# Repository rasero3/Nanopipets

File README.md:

# Nanopipets

MatLab(UART) --> FPGA(UART-SPI) --> DAC
ADC(SPI) --> FPGA(SPI-UART) --> MatLab(UART)

El DAC genera picos de la tension deseada cada 10Hz

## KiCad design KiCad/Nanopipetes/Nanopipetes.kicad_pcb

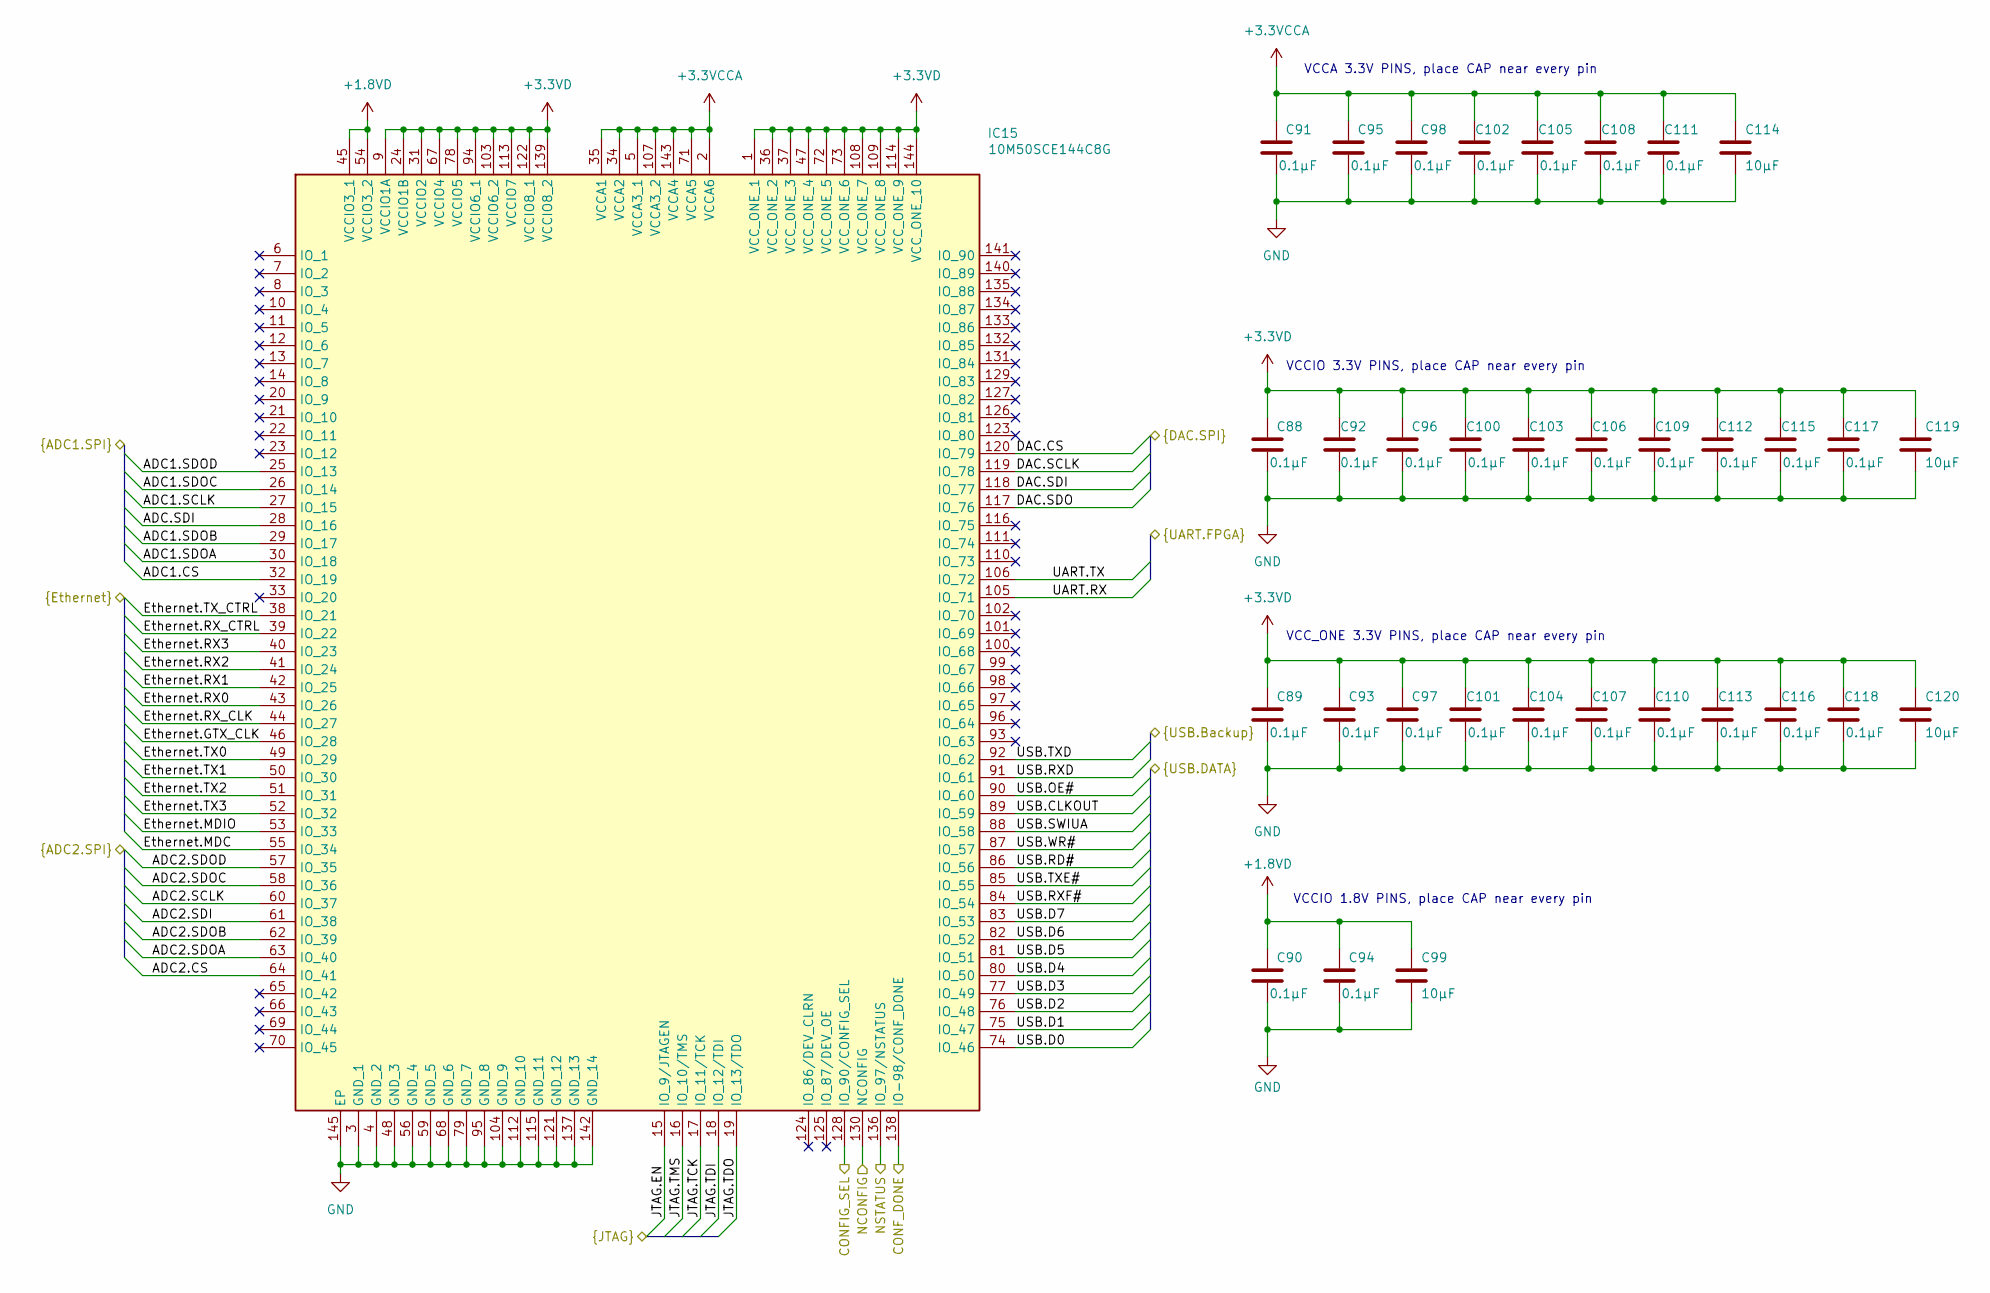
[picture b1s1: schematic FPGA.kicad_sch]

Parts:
C88, C89, C90, C91, C92, C93, C94, C95, C96, C97, C98, C100, C101, C102, C103, C104, C105, C106, C107, C108, C109, C110, C111, C112, C113, C115, C116, C117, C118: 0.1µF; C_0402_1005Metric; Mouser Part Number 581-0402YC104JAT4A
C99, C114, C119, C120: 10µF; C_0603_1608Metric; Mouser Part Number 80-C0603C106J3RACTU
IC15: 10M50SCE144C8G; QFP50P2200X2200X165-145N; Manufacturer_Part_Number 10M50SCE144C8G; Mouser Part Number 989-10M50SCE144C8G

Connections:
+1.8VD: C90.2, C94.2, C99.1, IC15.45 (VCCIO3_1), IC15.54 (VCCIO3_2); also elsewhere on the board
+3.3VCCA: C91.2, C95.2, C98.2, C102.2, C105.2, C108.2, C111.2, C114.1, IC15.2 (VCCA6), IC15.5 (VCCA3_1), IC15.34 (VCCA2), IC15.35 (VCCA1), IC15.71 (VCCA5), IC15.107 (VCCA3_2), IC15.143 (VCCA4); also elsewhere on the board
+3.3VD: C88.2, C89.2, C92.2, C93.2, C96.2, C97.2, C100.2, C101.2, C103.2, C104.2, C106.2, C107.2, C109.2, C110.2, C112.2, C113.2, C115.2, C116.2, C117.2, C118.2, C119.1, C120.1, IC15.1 (VCC_ONE_1), IC15.9 (VCCIO1A), IC15.24 (VCCIO1B), IC15.31 (VCCIO2), IC15.36 (VCC_ONE_2), IC15.37 (VCC_ONE_3), IC15.47 (VCC_ONE_4), IC15.67 (VCCIO4), IC15.72 (VCC_ONE_5), IC15.73 (VCC_ONE_6), IC15.78 (VCCIO5), IC15.94 (VCCIO6_1), IC15.103 (VCCIO6_2), IC15.108 (VCC_ONE_7), IC15.109 (VCC_ONE_8), IC15.113 (VCCIO7), IC15.114 (VCC_ONE_9), IC15.122 (VCCIO8_1), IC15.139 (VCCIO8_2), IC15.144 (VCC_ONE_10); also elsewhere on the board
/ADC1/ADC1.CS: IC15.32 (IO_19); also elsewhere on the board
/ADC1/ADC1.SCLK: IC15.27 (IO_15); also elsewhere on the board
/ADC1/ADC1.SDOA: IC15.30 (IO_18); also elsewhere on the board
/ADC1/ADC1.SDOB: IC15.29 (IO_17); also elsewhere on the board
/ADC1/ADC1.SDOC: IC15.26 (IO_14); also elsewhere on the board
/ADC1/ADC1.SDOD: IC15.25 (IO_13); also elsewhere on the board
/ADC1/ADC.SDI: IC15.28 (IO_16); also elsewhere on the board
/ADC2/ADC2.CS: IC15.64 (IO_41); also elsewhere on the board
/ADC2/ADC2.SCLK: IC15.60 (IO_37); also elsewhere on the board
/ADC2/ADC2.SDI: IC15.61 (IO_38); also elsewhere on the board
/ADC2/ADC2.SDOA: IC15.63 (IO_40); also elsewhere on the board
/ADC2/ADC2.SDOB: IC15.62 (IO_39); also elsewhere on the board
/ADC2/ADC2.SDOC: IC15.58 (IO_36); also elsewhere on the board
/ADC2/ADC2.SDOD: IC15.57 (IO_35); also elsewhere on the board
/Connectors/CONFIG_SEL: IC15.128 (IO_90/CONFIG_SEL); also elsewhere on the board
/Connectors/CONF_DONE: IC15.138 (IO-98/CONF_DONE); also elsewhere on the board
/Connectors/JTAG.EN: IC15.15 (IO_9/JTAGEN)
/Connectors/JTAG.TCK: IC15.17 (IO_11/TCK); also elsewhere on the board
/Connectors/JTAG.TDI: IC15.18 (IO_12/TDI); also elsewhere on the board
/Connectors/JTAG.TDO: IC15.19 (IO_13/TDO); also elsewhere on the board
/Connectors/JTAG.TMS: IC15.16 (IO_10/TMS); also elsewhere on the board
/Connectors/NCONFIG: IC15.130 (NCONFIG); also elsewhere on the board
/Connectors/NSTATUS: IC15.136 (IO_97/NSTATUS); also elsewhere on the board
/Connectors/UART.RX: IC15.105 (IO_71); also elsewhere on the board
/Connectors/UART.TX: IC15.106 (IO_72); also elsewhere on the board
/DAC/DAC.CS: IC15.120 (IO_79); also elsewhere on the board
/DAC/DAC.SCLK: IC15.119 (IO_78); also elsewhere on the board
/DAC/DAC.SDI: IC15.118 (IO_77); also elsewhere on the board
/DAC/DAC.SDO: IC15.117 (IO_76); also elsewhere on the board
/Ethernet/Ethernet.GTX_CLK: IC15.46 (IO_28); also elsewhere on the board
/Ethernet/Ethernet.MDC: IC15.55 (IO_34); also elsewhere on the board
/Ethernet/Ethernet.MDIO: IC15.53 (IO_33); also elsewhere on the board
/Ethernet/Ethernet.RX0: IC15.43 (IO_26); also elsewhere on the board
/Ethernet/Ethernet.RX1: IC15.42 (IO_25); also elsewhere on the board
/Ethernet/Ethernet.RX2: IC15.41 (IO_24); also elsewhere on the board
/Ethernet/Ethernet.RX3: IC15.40 (IO_23); also elsewhere on the board
/Ethernet/Ethernet.RX_CLK: IC15.44 (IO_27); also elsewhere on the board
/Ethernet/Ethernet.RX_CTRL: IC15.39 (IO_22); also elsewhere on the board
/Ethernet/Ethernet.TX0: IC15.49 (IO_29); also elsewhere on the board
/Ethernet/Ethernet.TX1: IC15.50 (IO_30); also elsewhere on the board
/Ethernet/Ethernet.TX2: IC15.51 (IO_31); also elsewhere on the board
/Ethernet/Ethernet.TX3: IC15.52 (IO_32); also elsewhere on the board
/Ethernet/Ethernet.TX_CTRL: IC15.38 (IO_21); also elsewhere on the board
/FPGA/USB.CLKOUT: IC15.89 (IO_59); also elsewhere on the board
/FPGA/USB.D0: IC15.74 (IO_46); also elsewhere on the board
/FPGA/USB.D1: IC15.75 (IO_47); also elsewhere on the board
/FPGA/USB.D2: IC15.76 (IO_48); also elsewhere on the board
/FPGA/USB.D3: IC15.77 (IO_49); also elsewhere on the board
/FPGA/USB.D4: IC15.80 (IO_50); also elsewhere on the board
/FPGA/USB.D5: IC15.81 (IO_51); also elsewhere on the board
/FPGA/USB.D6: IC15.82 (IO_52); also elsewhere on the board
/FPGA/USB.D7: IC15.83 (IO_53); also elsewhere on the board
/FPGA/USB.OE#: IC15.90 (IO_60); also elsewhere on the board
/FPGA/USB.RD#: IC15.86 (IO_56); also elsewhere on the board
/FPGA/USB.RXD: IC15.91 (IO_61); also elsewhere on the board
/FPGA/USB.RXF#: IC15.84 (IO_54); also elsewhere on the board
/FPGA/USB.SWIUA: IC15.88 (IO_58); also elsewhere on the board
/FPGA/USB.TXD: IC15.92 (IO_62); also elsewhere on the board
/FPGA/USB.TXE#: IC15.85 (IO_55); also elsewhere on the board
/FPGA/USB.WR#: IC15.87 (IO_57); also elsewhere on the board
GND: C88.1, C89.1, C90.1, C91.1, C92.1, C93.1, C94.1, C95.1, C96.1, C97.1, C98.1, C99.2, C100.1, C101.1, C102.1, C103.1, C104.1, C105.1, C106.1, C107.1, C108.1, C109.1, C110.1, C111.1, C112.1, C113.1, C114.2, C115.1, C116.1, C117.1, C118.1, C119.2, C120.2, IC15.3 (GND_1), IC15.4 (GND_2), IC15.48 (GND_3), IC15.56 (GND_4), IC15.59 (GND_5), IC15.68 (GND_6), IC15.79 (GND_7), IC15.95 (GND_8), IC15.104 (GND_9), IC15.112 (GND_10), IC15.115 (GND_11), IC15.121 (GND_12), IC15.137 (GND_13), IC15.142 (GND_14), IC15.145 (EP); also elsewhere on the board

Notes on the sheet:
VCC_ONE 3.3V PINS, place CAP near every pin
VCCA 3.3V PINS, place CAP near every pin
VCCIO 1.8V PINS, place CAP near every pin
VCCIO 3.3V PINS, place CAP near every pin

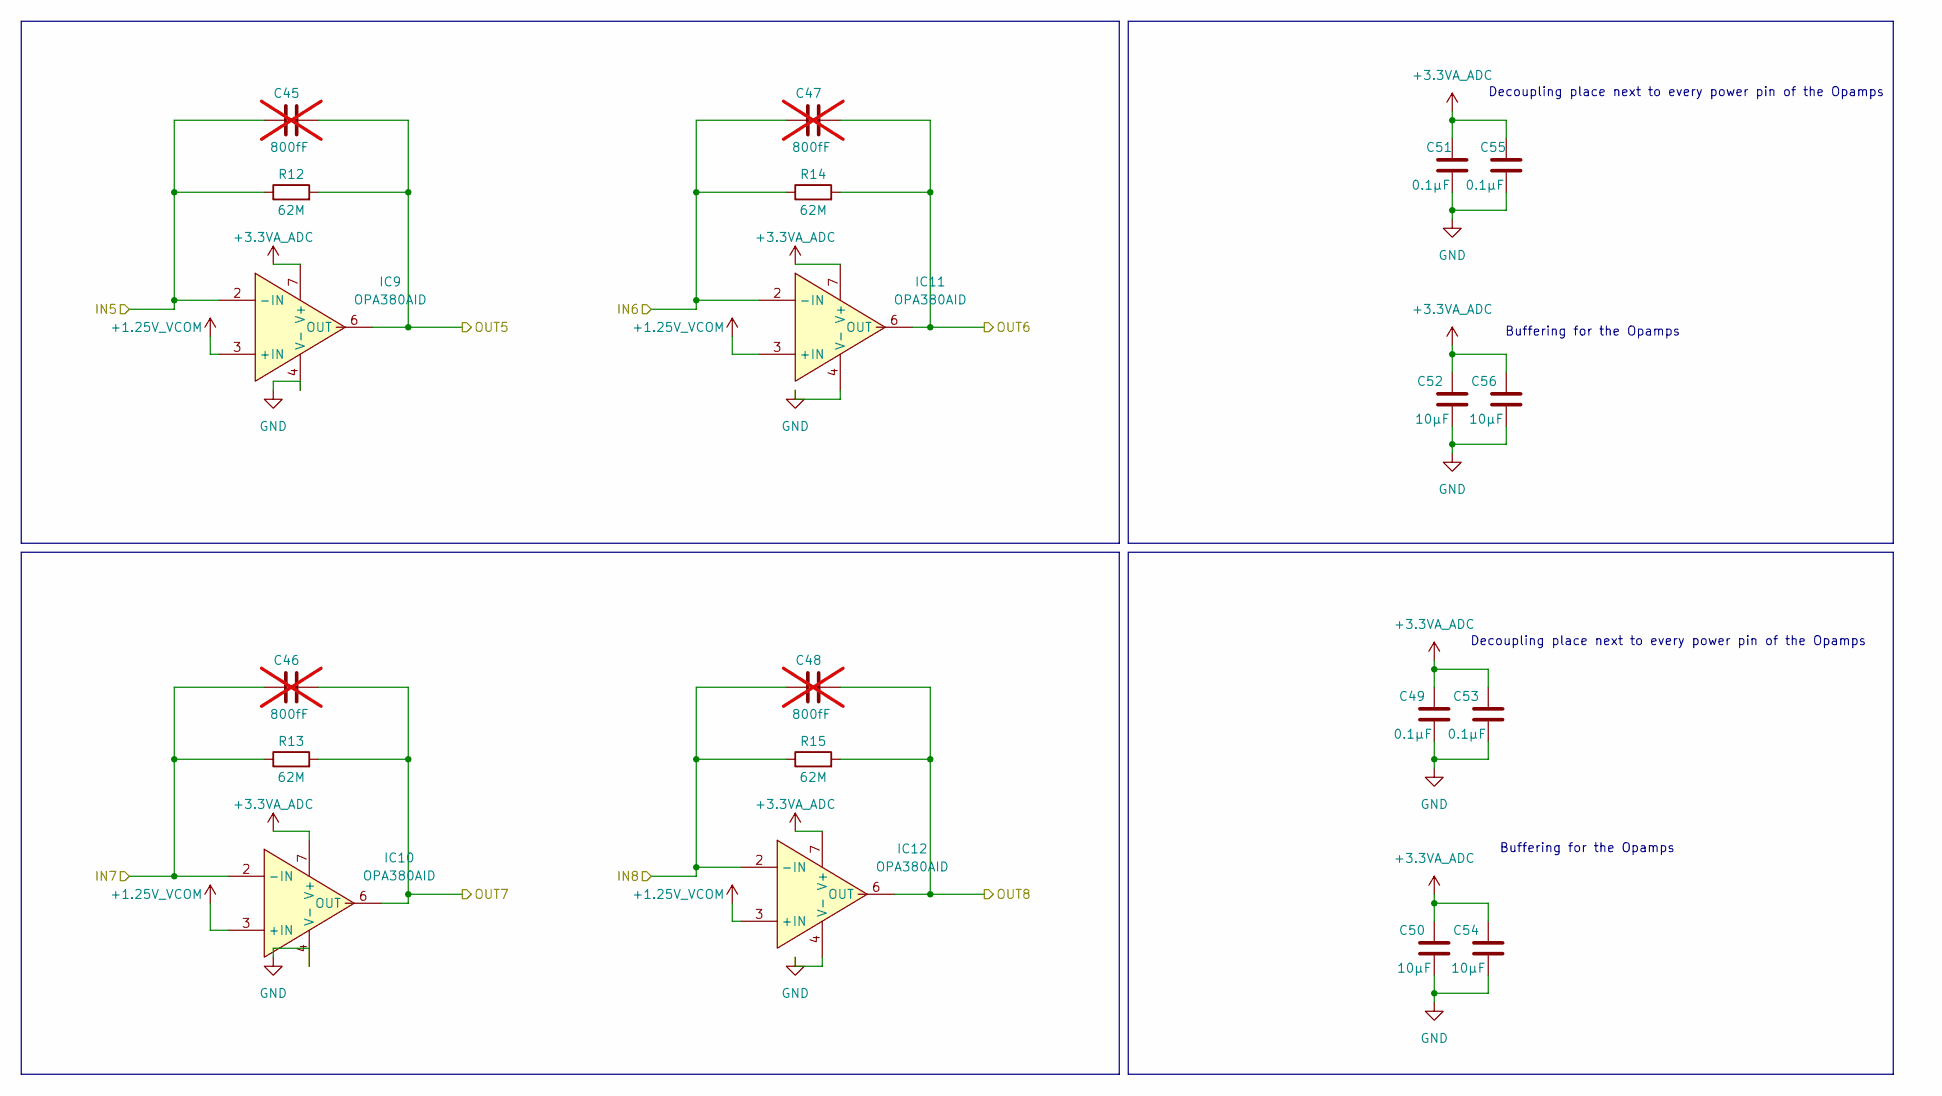
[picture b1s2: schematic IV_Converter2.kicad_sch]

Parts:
C45, C46, C47, C48: 800fF; C_0402_1005Metric; Mouser Part Number 81-GCM1555C2AR80BE2D; not fitted
C49, C51, C53, C55: 0.1µF; C_0402_1005Metric; Mouser Part Number 581-0402YC104JAT4A
C50, C52, C54, C56: 10µF; C_0603_1608Metric; Mouser Part Number 80-C0603C106J3RACTU
IC9, IC10, IC11, IC12: OPA380AID; SOIC127P600X175-8N; Mouser Part Number 595-OPA380AID
R12, R13, R14, R15: 62M; R_0603_1608Metric; Mouser Part Number 71-RCW120662M0JPEAHR

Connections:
+1.25V_VCOM: IC9.3 (+IN), IC10.3 (+IN), IC11.3 (+IN), IC12.3 (+IN); also elsewhere on the board
+3.3VA_ADC: C49.1, C50.1, C51.1, C52.1, C53.1, C54.1, C55.1, C56.1, IC9.7 (V+), IC10.7 (V+), IC11.7 (V+), IC12.7 (V+); also elsewhere on the board
/ADC2/IN5: C45.2, IC9.6 (OUT), R12.2; also elsewhere on the board
/ADC2/IN6: C47.2, IC11.6 (OUT), R14.2; also elsewhere on the board
/ADC2/IN7: C46.2, IC10.6 (OUT), R13.2; also elsewhere on the board
/ADC2/IN8: C48.2, IC12.6 (OUT), R15.2; also elsewhere on the board
/Connectors/IN5: C45.1, IC9.2 (-IN), R12.1; also elsewhere on the board
/Connectors/IN6: C47.1, IC11.2 (-IN), R14.1; also elsewhere on the board
/Connectors/IN7: C46.1, IC10.2 (-IN), R13.1; also elsewhere on the board
/Connectors/IN8: C48.1, IC12.2 (-IN), R15.1; also elsewhere on the board
GND: C49.2, C50.2, C51.2, C52.2, C53.2, C54.2, C55.2, C56.2, IC9.4 (V-), IC10.4 (V-), IC11.4 (V-), IC12.4 (V-); also elsewhere on the board

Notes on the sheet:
Buffering for the Opamps
Decoupling place next to every power pin of the Opamps

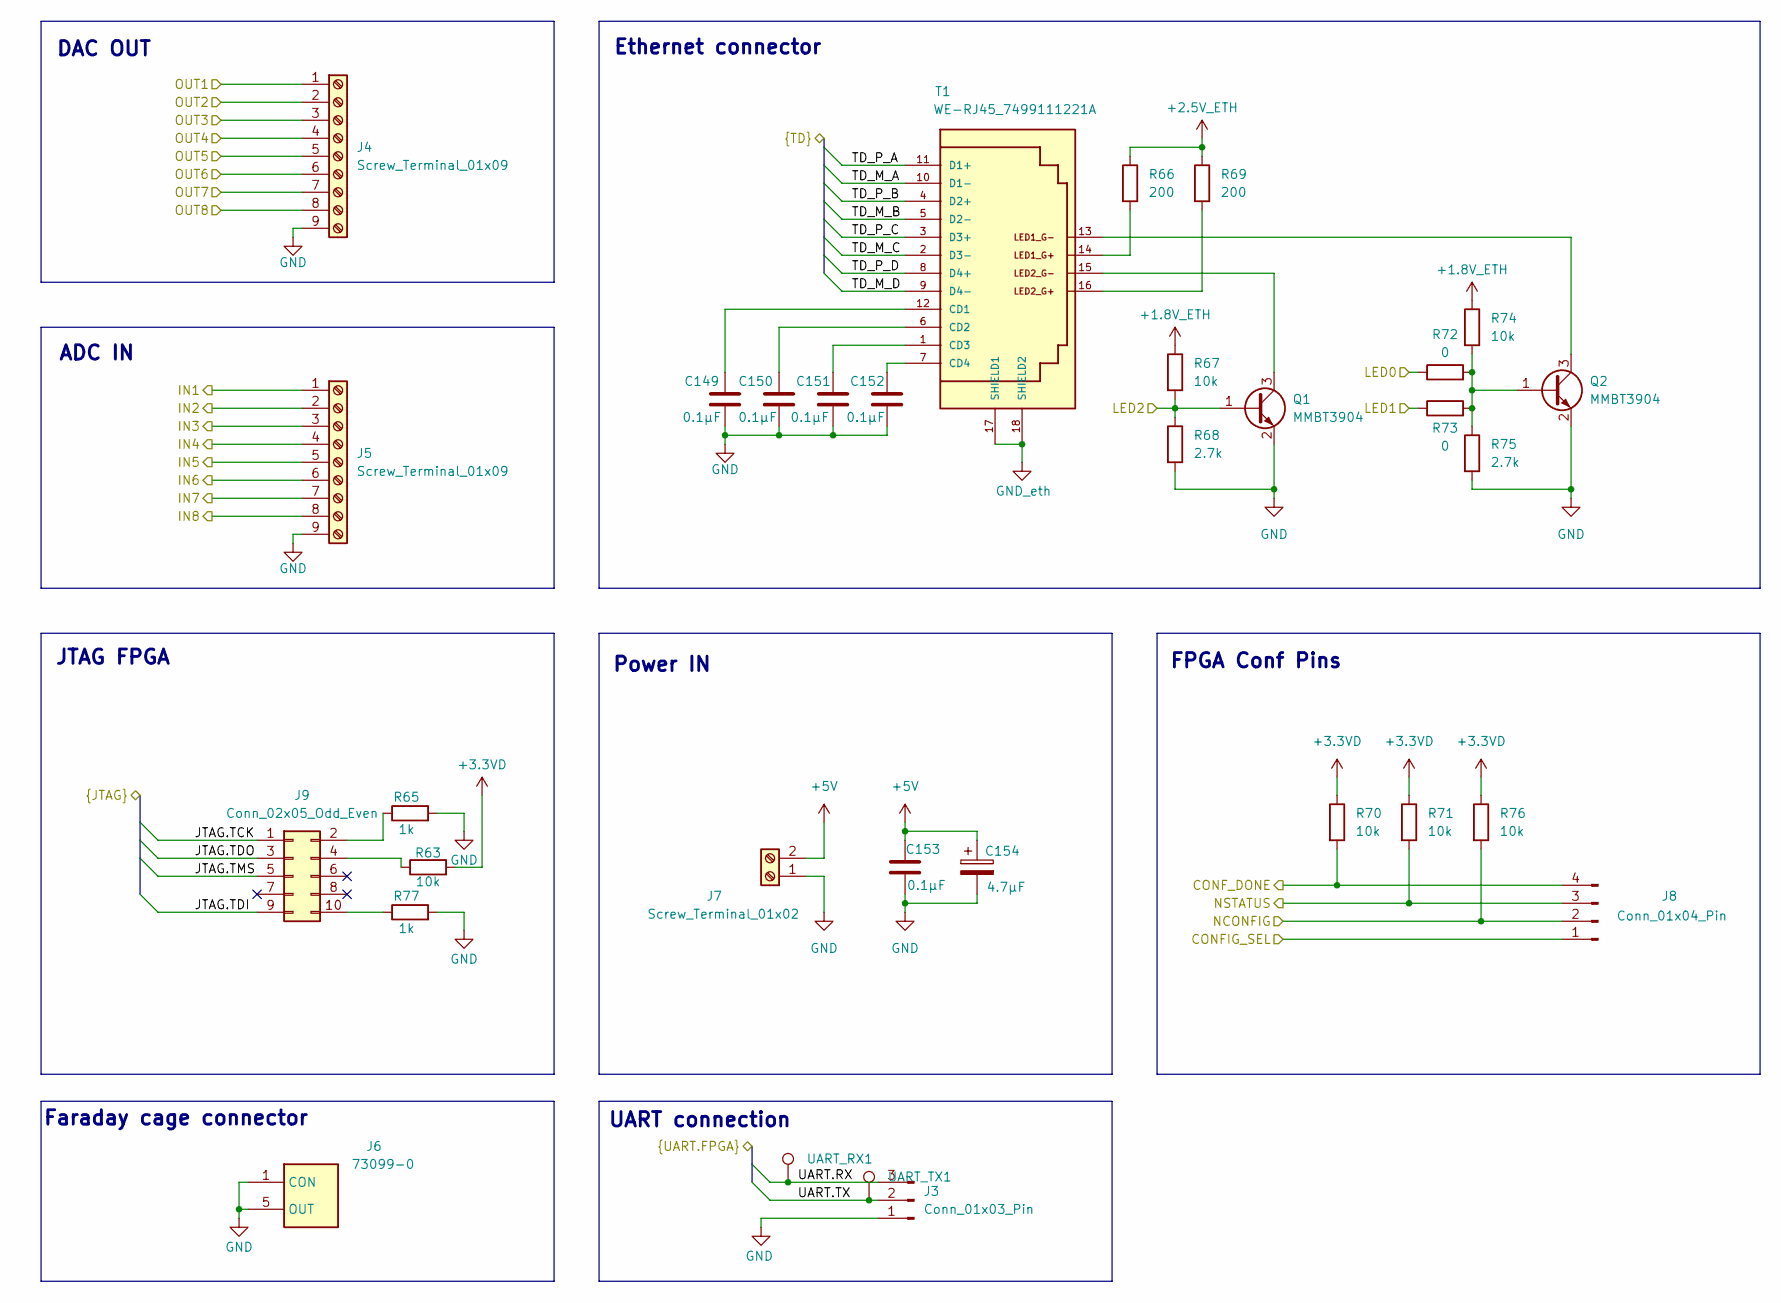
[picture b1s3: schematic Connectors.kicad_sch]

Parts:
C149, C150, C151, C152, C153: 0.1µF; C_0402_1005Metric; Mouser Part Number 581-0402YC104JAT4A
C154: 4.7µF; CP_EIA-3216-12_Kemet-S; Mouser Part Number 71-293D475X5010A2TE3
J3: Conn_01x03_Pin; PinHeader_1x03_P2.54mm_Vertical
J4, J5: Screw_Terminal_01x09; TerminalBlock_Phoenix_MKDS-1,5-9-5.08_1x09_P5.08mm_Horizont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
J6: 73099-0; 730990; Manufacturer_Part_Number 73099-0; Mouser Part Number 565-73099-0
J7: Screw_Terminal_01x02; TerminalBlock_Phoenix_MKDS-1,5-2-5.08_1x02_P5.08mm_Horizont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
J8: Conn_01x04_Pin; PinHeader_1x04_P2.54mm_Vertical
J9: Conn_02x05_Odd_Even; PinHeader_2x05_P2.54mm_Vertical
Q1, Q2: MMBT3904; SOT-23
R63, R67, R70, R71, R74, R76: 10k; R_0603_1608Metric; Mouser Part Number 71-RCA060310K0JNEA
R65, R77: 1k; R_0603_1608Metric; Mouser Part Number 71-CRCW06031K00JNED
R66, R69: 200; R_0603_1608Metric; Mouser Part Number 303-CQ03WAJ0201T5E
R68, R75: 2.7k; R_0603_1608Metric; Mouser Part Number 603-AR0603JR-072K7L
R72: 0; R_0603_1608Metric; Mouser Part Number 791-WR06X000PTR
R73: 0; R_0603_1608Metric
T1: WE-RJ45_7499111221A; 7499111221A; Mouser Part Number 710-7499111221A
UART_RX1: TestPoint; TestPoint_Keystone_5000-5004_Miniature
UART_TX1: TestPoint; TestPoint_Keystone_5000-5004_Miniature

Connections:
+1.8VD: R67.1, R74.1; also elsewhere on the board
+2.5V_ETH: R66.1, R69.1; also elsewhere on the board
+3.3VD: R63.2, R70.1, R71.1, R76.1; also elsewhere on the board
+5V: C153.2, C154.1, J7.2; also elsewhere on the board
/Connectors/CONFIG_SEL: J8.1; also elsewhere on the board
/Connectors/CONF_DONE: J8.4, R70.2; also elsewhere on the board
/Connectors/IN1: J5.1; also elsewhere on the board
/Connectors/IN2: J5.2; also elsewhere on the board
/Connectors/IN3: J5.3; also elsewhere on the board
/Connectors/IN4: J5.4; also elsewhere on the board
/Connectors/IN5: J5.5; also elsewhere on the board
/Connectors/IN6: J5.6; also elsewhere on the board
/Connectors/IN7: J5.7; also elsewhere on the board
/Connectors/IN8: J5.8; also elsewhere on the board
/Connectors/JTAG.TCK: J9.1; also elsewhere on the board
/Connectors/JTAG.TDI: J9.9; also elsewhere on the board
/Connectors/JTAG.TDO: J9.3; also elsewhere on the board
/Connectors/JTAG.TMS: J9.5; also elsewhere on the board
/Connectors/LED0: R72.1; also elsewhere on the board
/Connectors/LED1: R73.1; also elsewhere on the board
/Connectors/LED2: Q1.1 (B), R67.2, R68.1; also elsewhere on the board
/Connectors/NCONFIG: J8.2, R76.2; also elsewhere on the board
/Connectors/NSTATUS: J8.3, R71.2; also elsewhere on the board
/Connectors/OUT1: J4.1; also elsewhere on the board
/Connectors/OUT2: J4.2; also elsewhere on the board
/Connectors/OUT3: J4.3; also elsewhere on the board
/Connectors/OUT4: J4.4; also elsewhere on the board
/Connectors/OUT5: J4.5; also elsewhere on the board
/Connectors/OUT6: J4.6; also elsewhere on the board
/Connectors/OUT7: J4.7; also elsewhere on the board
/Connectors/OUT8: J4.8; also elsewhere on the board
/Connectors/TD_M_A: T1.10 (D1-); also elsewhere on the board
/Connectors/TD_M_B: T1.5 (D2-); also elsewhere on the board
/Connectors/TD_M_C: T1.2 (D3-); also elsewhere on the board
/Connectors/TD_M_D: T1.9 (D4-); also elsewhere on the board
/Connectors/TD_P_A: T1.11 (D1+); also elsewhere on the board
/Connectors/TD_P_B: T1.4 (D2+); also elsewhere on the board
/Connectors/TD_P_C: T1.3 (D3+); also elsewhere on the board
/Connectors/TD_P_D: T1.8 (D4+); also elsewhere on the board
/Connectors/UART.RX: J3.3, UART_RX1.1; also elsewhere on the board
/Connectors/UART.TX: J3.2, UART_TX1.1; also elsewhere on the board
GND: C149.2, C150.2, C151.2, C152.2, C153.1, C154.2, J3.1, J4.9, J5.9, J6.1 (CON), J6.2, J6.3, J6.4, J6.5 (OUT), J7.1, Q1.2 (E), Q2.2 (E), R65.2, R68.2, R75.2, R77.2, T1.17 (SHIELD1), T1.18 (SHIELD2); also elsewhere on the board
unnamed: J9.2, R65.1
unnamed: J9.4, R63.1
unnamed: J9.10, R77.1
unnamed: Q1.3 (C), T1.15
unnamed: Q2.1 (B), R72.2, R73.2, R74.2, R75.1
unnamed: Q2.3 (C), T1.13
unnamed: R66.2, T1.14
unnamed: R69.2, T1.16
unnamed: C149.1, T1.12 (CD1)
unnamed: C150.1, T1.6 (CD2)
unnamed: C151.1, T1.1 (CD3)
unnamed: C152.1, T1.7 (CD4)

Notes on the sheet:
UART connection
Faraday cage connector
Ethernet connector
ADC IN
JTAG FPGA
Power IN
DAC OUT
FPGA Conf Pins

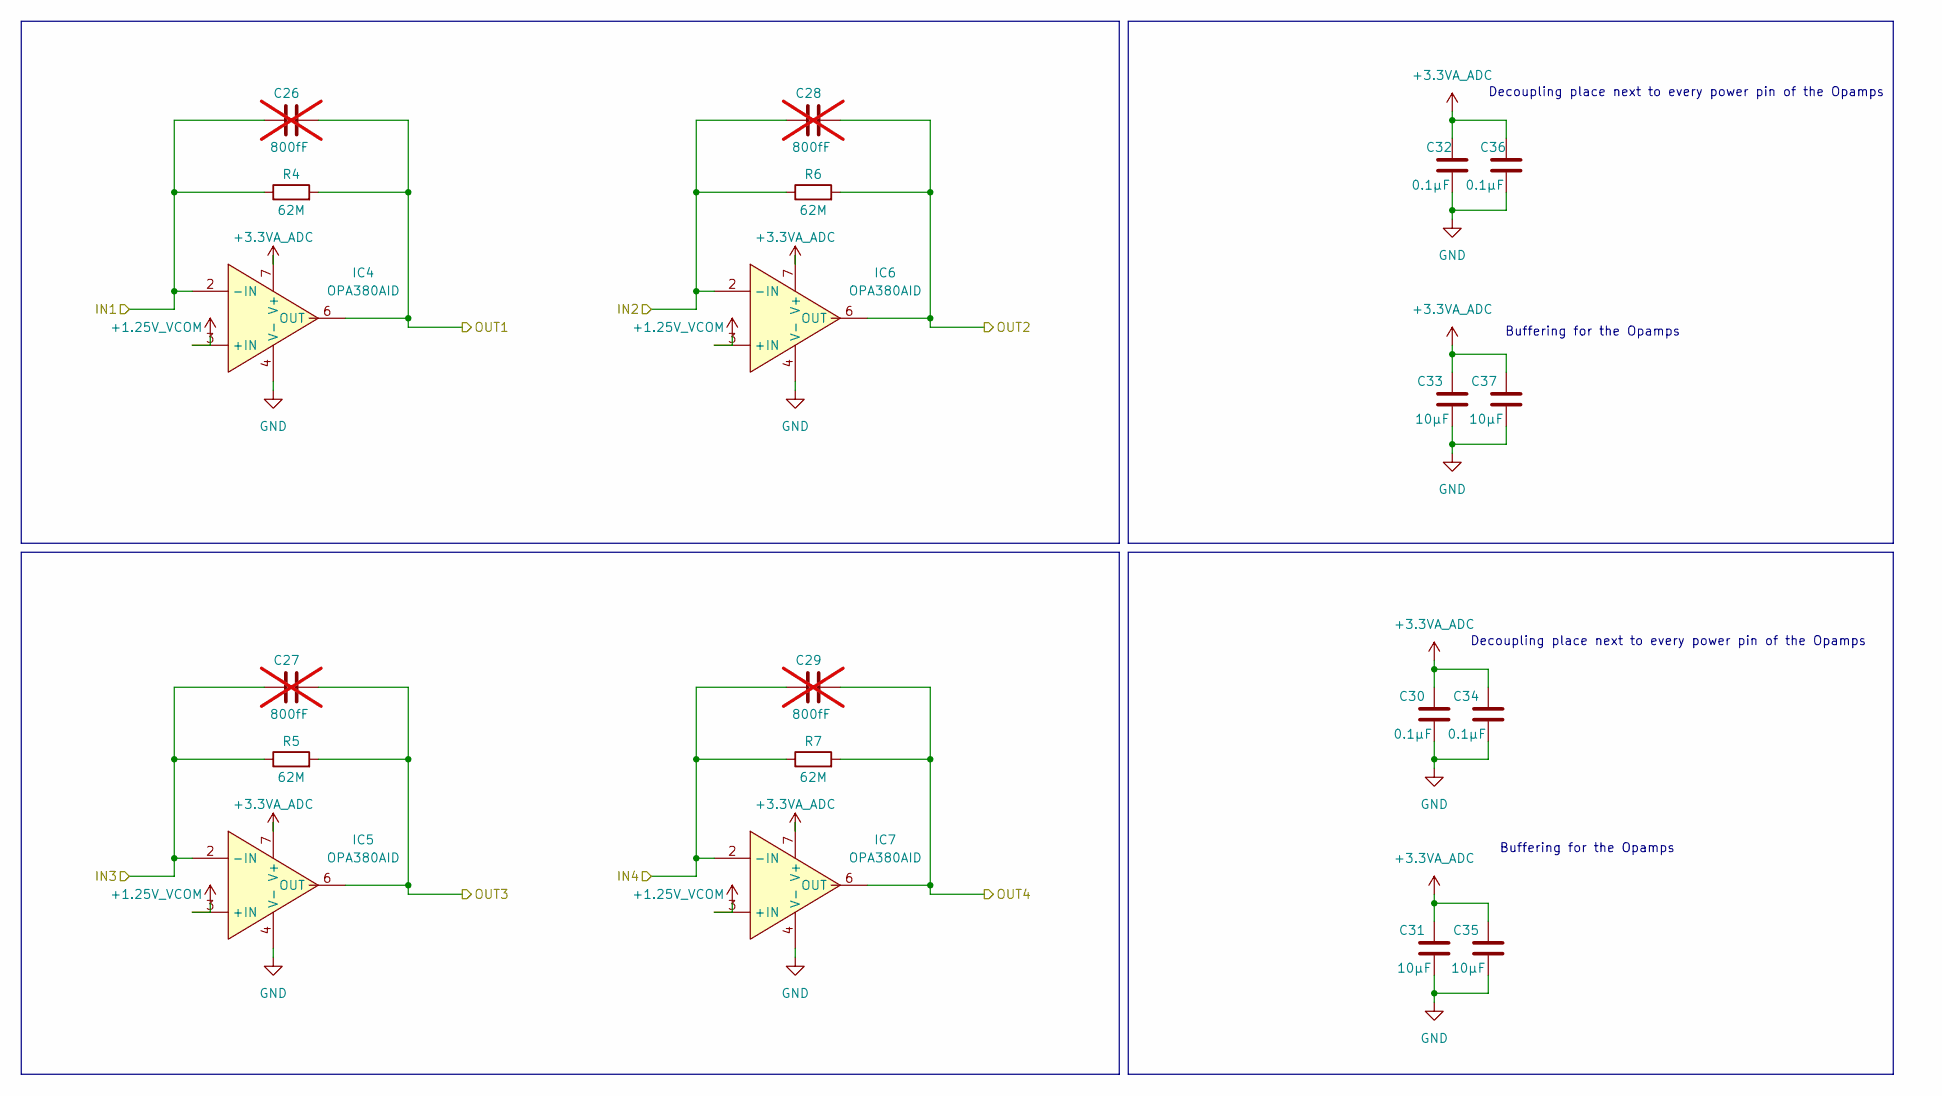
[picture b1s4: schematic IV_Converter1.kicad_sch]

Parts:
C26, C27, C28, C29: 800fF; C_0402_1005Metric; Mouser Part Number 81-GCM1555C2AR80BE2D; not fitted
C30, C32, C34, C36: 0.1µF; C_0402_1005Metric; Mouser Part Number 581-0402YC104JAT4A
C31, C33, C35, C37: 10µF; C_0603_1608Metric; Mouser Part Number 80-C0603C106J3RACTU
IC4, IC5, IC6, IC7: OPA380AID; SOIC127P600X175-8N; Mouser Part Number 595-OPA380AID
R4, R5, R6, R7: 62M; R_1206_3216Metric; Mouser Part Number 71-RCW120662M0JPEAHR

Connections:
+1.25V_VCOM: IC4.3 (+IN), IC5.3 (+IN), IC6.3 (+IN), IC7.3 (+IN); also elsewhere on the board
+3.3VA_ADC: C30.1, C31.1, C32.1, C33.1, C34.1, C35.1, C36.1, C37.1, IC4.7 (V+), IC5.7 (V+), IC6.7 (V+), IC7.7 (V+); also elsewhere on the board
/ADC1/IN1: C26.2, IC4.6 (OUT), R4.2; also elsewhere on the board
/ADC1/IN2: C28.2, IC6.6 (OUT), R6.2; also elsewhere on the board
/ADC1/IN3: C27.2, IC5.6 (OUT), R5.2; also elsewhere on the board
/ADC1/IN4: C29.2, IC7.6 (OUT), R7.2; also elsewhere on the board
/Connectors/IN1: C26.1, IC4.2 (-IN), R4.1; also elsewhere on the board
/Connectors/IN2: C28.1, IC6.2 (-IN), R6.1; also elsewhere on the board
/Connectors/IN3: C27.1, IC5.2 (-IN), R5.1; also elsewhere on the board
/Connectors/IN4: C29.1, IC7.2 (-IN), R7.1; also elsewhere on the board
GND: C30.2, C31.2, C32.2, C33.2, C34.2, C35.2, C36.2, C37.2, IC4.4 (V-), IC5.4 (V-), IC6.4 (V-), IC7.4 (V-); also elsewhere on the board

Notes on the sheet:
Decoupling place next to every power pin of the Opamps
Buffering for the Opamps

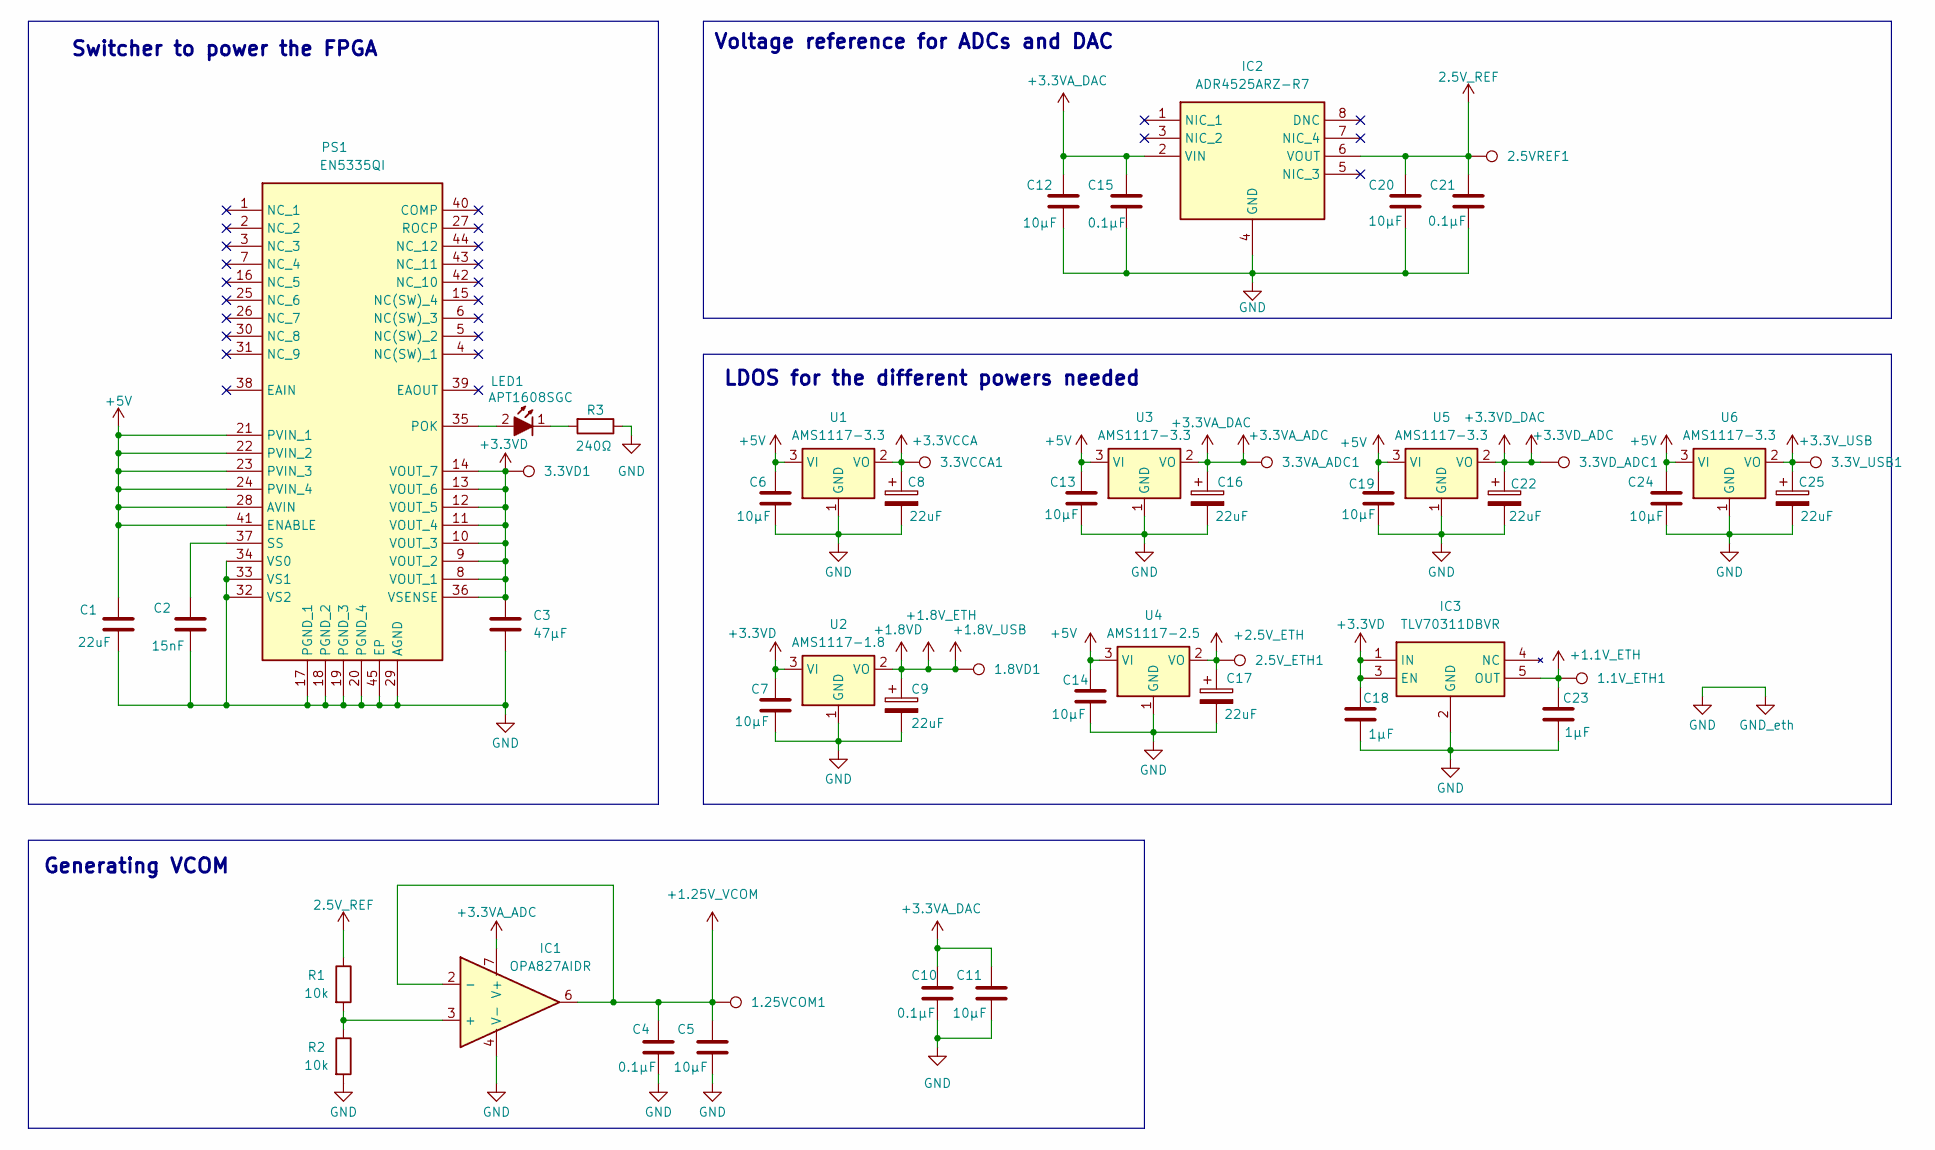
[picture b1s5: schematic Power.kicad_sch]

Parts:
1.1V_ETH1, 1.8VD1, 1.25VCOM1, 2.5VREF1, 2.5V_ETH1, 3.3VA_ADC1, 3.3VCCA1, 3.3VD1, 3.3VD_ADC1, 3.3V_USB1: TestPoint; TestPoint_Keystone_5000-5004_Miniature
C1: 22uF; C_0805_2012Metric; Mouser Part Number 791-1206X226J6R3CT
C2: 15nF; C_0402_1005Metric; Mouser Part Number 77-VJ0402Y153JXJCBC
C3: 47µF; C_1206_3216Metric; Mouser Part Number GGM32ED70J476KE02L
C4, C10, C15, C21: 0.1µF; C_0402_1005Metric; Mouser Part Number 581-0402YC104JAT4A
C5, C6, C7, C11, C12, C13, C14, C19, C20, C24: 10µF; C_0603_1608Metric; Mouser Part Number 80-C0603C106J3RACTU
C8, C9, C16, C17, C22, C25: 22uF; CP_EIA-3216-18_Kemet-A; Mouser Part Number 581-TBJB226J006CS700
C18, C23: 1µF; C_0603_1608Metric; Mouser Part Number 581-KGM15BR71A105JT
IC1: OPA827AIDR; SOIC127P600X175-8N; Manufacturer_Part_Number OPA827AIDR; Mouser Part Number 595-OPA827AIDR
IC2: ADR4525ARZ-R7; SOIC127P600X175-8N; Manufacturer_Part_Number ADR4525ARZ-R7; Mouser Part Number 584-ADR4525ARZ-R7
IC3: TLV70311DBVR; SOT95P280X145-5N; Manufacturer_Part_Number TLV70311DBVR; Mouser Part Number 595-TLV70311DBVR
LED1: APT1608SGC; LEDC1608X85N; Manufacturer_Part_Number APT1608SGC; Mouser Part Number 604-APT1608SGC
PS1: EN5335QI; Manufacturer_Part_Number EN5335QI; Mouser Part Number 884-EN5335QI
R1, R2: 10k; R_0603_1608Metric; Mouser Part Number 71-RCA060310K0JNEA
R3: 240Ω; R_0603_1608Metric; Mouser Part Number 603-AR0603JR-07240RL
U1, U3, U5, U6: AMS1117-3.3; SOT-223-3_TabPin2
U2: AMS1117-1.8; SOT-223-3_TabPin2
U4: AMS1117-2.5; SOT-223-3_TabPin2

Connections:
2.5V_REF: 2.5VREF1.1, C20.1, C21.1, IC2.6 (VOUT), R1.1; also elsewhere on the board
+1.1V_ETH: 1.1V_ETH1.1, C23.1, IC3.5 (OUT); also elsewhere on the board
+1.8VD: 1.8VD1.1, C9.1, U2.2 (VO); also elsewhere on the board
+1.25V_VCOM: 1.25VCOM1.1, C4.1, C5.1, IC1.2 (-), IC1.6; also elsewhere on the board
+2.5V_ETH: 2.5V_ETH1.1, C17.1, U4.2 (VO); also elsewhere on the board
+3.3VA_ADC: 3.3VA_ADC1.1, C10.1, C11.1, C12.1, C15.1, C16.1, IC1.7 (V+), IC2.2 (VIN), U3.2 (VO); also elsewhere on the board
+3.3VCCA: 3.3VCCA1.1, C8.1, U1.2 (VO); also elsewhere on the board
+3.3VD: 3.3VD1.1, C3.1, C7.1, C18.1, IC3.1 (IN), IC3.3 (EN), PS1.8 (VOUT_1), PS1.9 (VOUT_2), PS1.10 (VOUT_3), PS1.11 (VOUT_4), PS1.12 (VOUT_5), PS1.13 (VOUT_6), PS1.14 (VOUT_7), PS1.36 (VSENSE), U2.3 (VI); also elsewhere on the board
+3.3VD_ADC: 3.3VD_ADC1.1, C22.1, U5.2 (VO); also elsewhere on the board
+3.3V_USB: 3.3V_USB1.1, C25.1, U6.2 (VO); also elsewhere on the board
+5V: C1.1, C6.1, C13.1, C14.1, C19.1, C24.1, PS1.21 (PVIN_1), PS1.22 (PVIN_2), PS1.23 (PVIN_3), PS1.24 (PVIN_4), PS1.28 (AVIN), PS1.41 (ENABLE), U1.3 (VI), U3.3 (VI), U4.3 (VI), U5.3 (VI), U6.3 (VI); also elsewhere on the board
GND: C1.2, C2.2, C3.2, C4.2, C5.2, C6.2, C7.2, C8.2, C9.2, C10.2, C11.2, C12.2, C13.2, C14.2, C15.2, C16.2, C17.2, C18.2, C19.2, C20.2, C21.2, C22.2, C23.2, C24.2, C25.2, IC1.4 (V-), IC2.4 (GND), IC3.2 (GND), PS1.17 (PGND_1), PS1.18 (PGND_2), PS1.19 (PGND_3), PS1.20 (PGND_4), PS1.29 (AGND), PS1.32 (VS2), PS1.33 (VS1), PS1.34 (VS0), PS1.45 (EP), R2.2, R3.1, U1.1 (GND), U2.1 (GND), U3.1 (GND), U4.1 (GND), U5.1 (GND), U6.1 (GND); also elsewhere on the board
unnamed: IC1.3 (+), R1.2, R2.1
unnamed: LED1.2 (A), PS1.35 (POK)
unnamed: LED1.1 (K), R3.2
unnamed: C2.1, PS1.37 (SS)

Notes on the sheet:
Generating VCOM
LDOS for the different powers needed
Voltage reference for ADCs and DAC
Switcher to power the FPGA
